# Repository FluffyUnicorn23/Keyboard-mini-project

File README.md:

PCB made with KiCAD, currently working on keyboard case and firmware

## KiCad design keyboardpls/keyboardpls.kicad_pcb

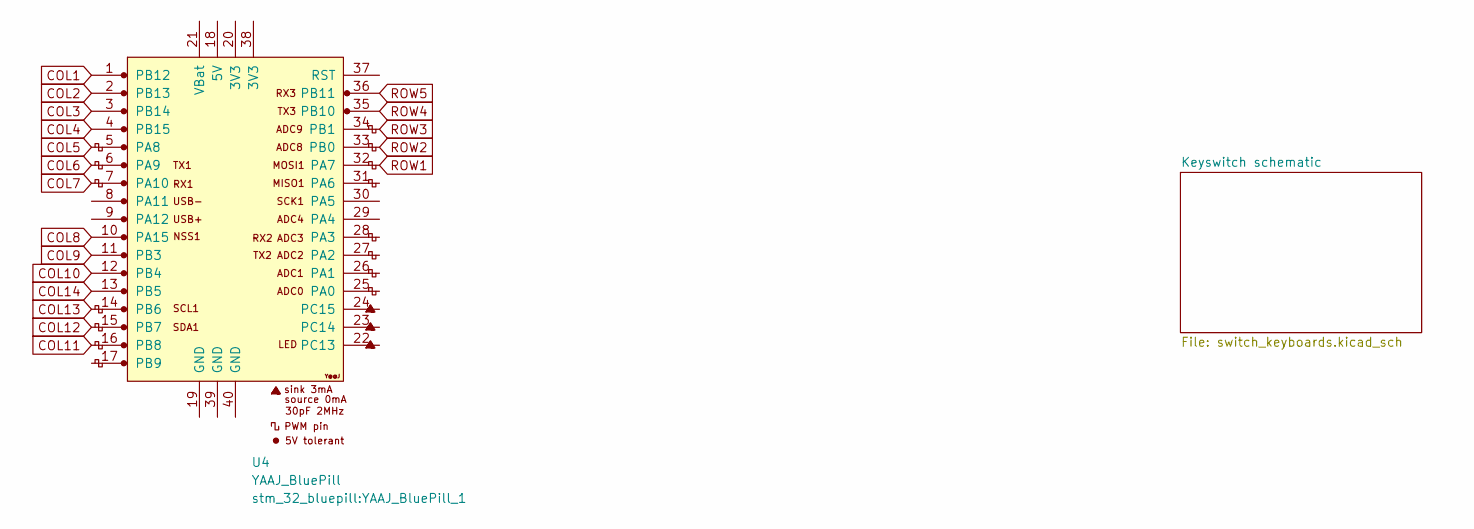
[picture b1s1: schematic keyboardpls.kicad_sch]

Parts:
U4: YAAJ_BluePill; YAAJ_BluePill_1

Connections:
COL1: U4.1 (PB12); also elsewhere on the board
COL2: U4.2 (PB13); also elsewhere on the board
COL3: U4.3 (PB14); also elsewhere on the board
COL4: U4.4 (PB15); also elsewhere on the board
COL5: U4.5 (PA8); also elsewhere on the board
COL6: U4.6 (PA9); also elsewhere on the board
COL7: U4.7 (PA10); also elsewhere on the board
COL8: U4.10 (PA15); also elsewhere on the board
COL9: U4.11 (PB3); also elsewhere on the board
COL10: U4.12 (PB4); also elsewhere on the board
COL11: U4.16 (PB8); also elsewhere on the board
COL12: U4.15 (PB7); also elsewhere on the board
COL13: U4.14 (PB6); also elsewhere on the board
COL14: U4.13 (PB5); also elsewhere on the board
ROW1: U4.32 (PA7); also elsewhere on the board
ROW2: U4.33 (PB0); also elsewhere on the board
ROW3: U4.34 (PB1); also elsewhere on the board
ROW4: U4.35 (PB10); also elsewhere on the board
ROW5: U4.36 (PB11); also elsewhere on the board

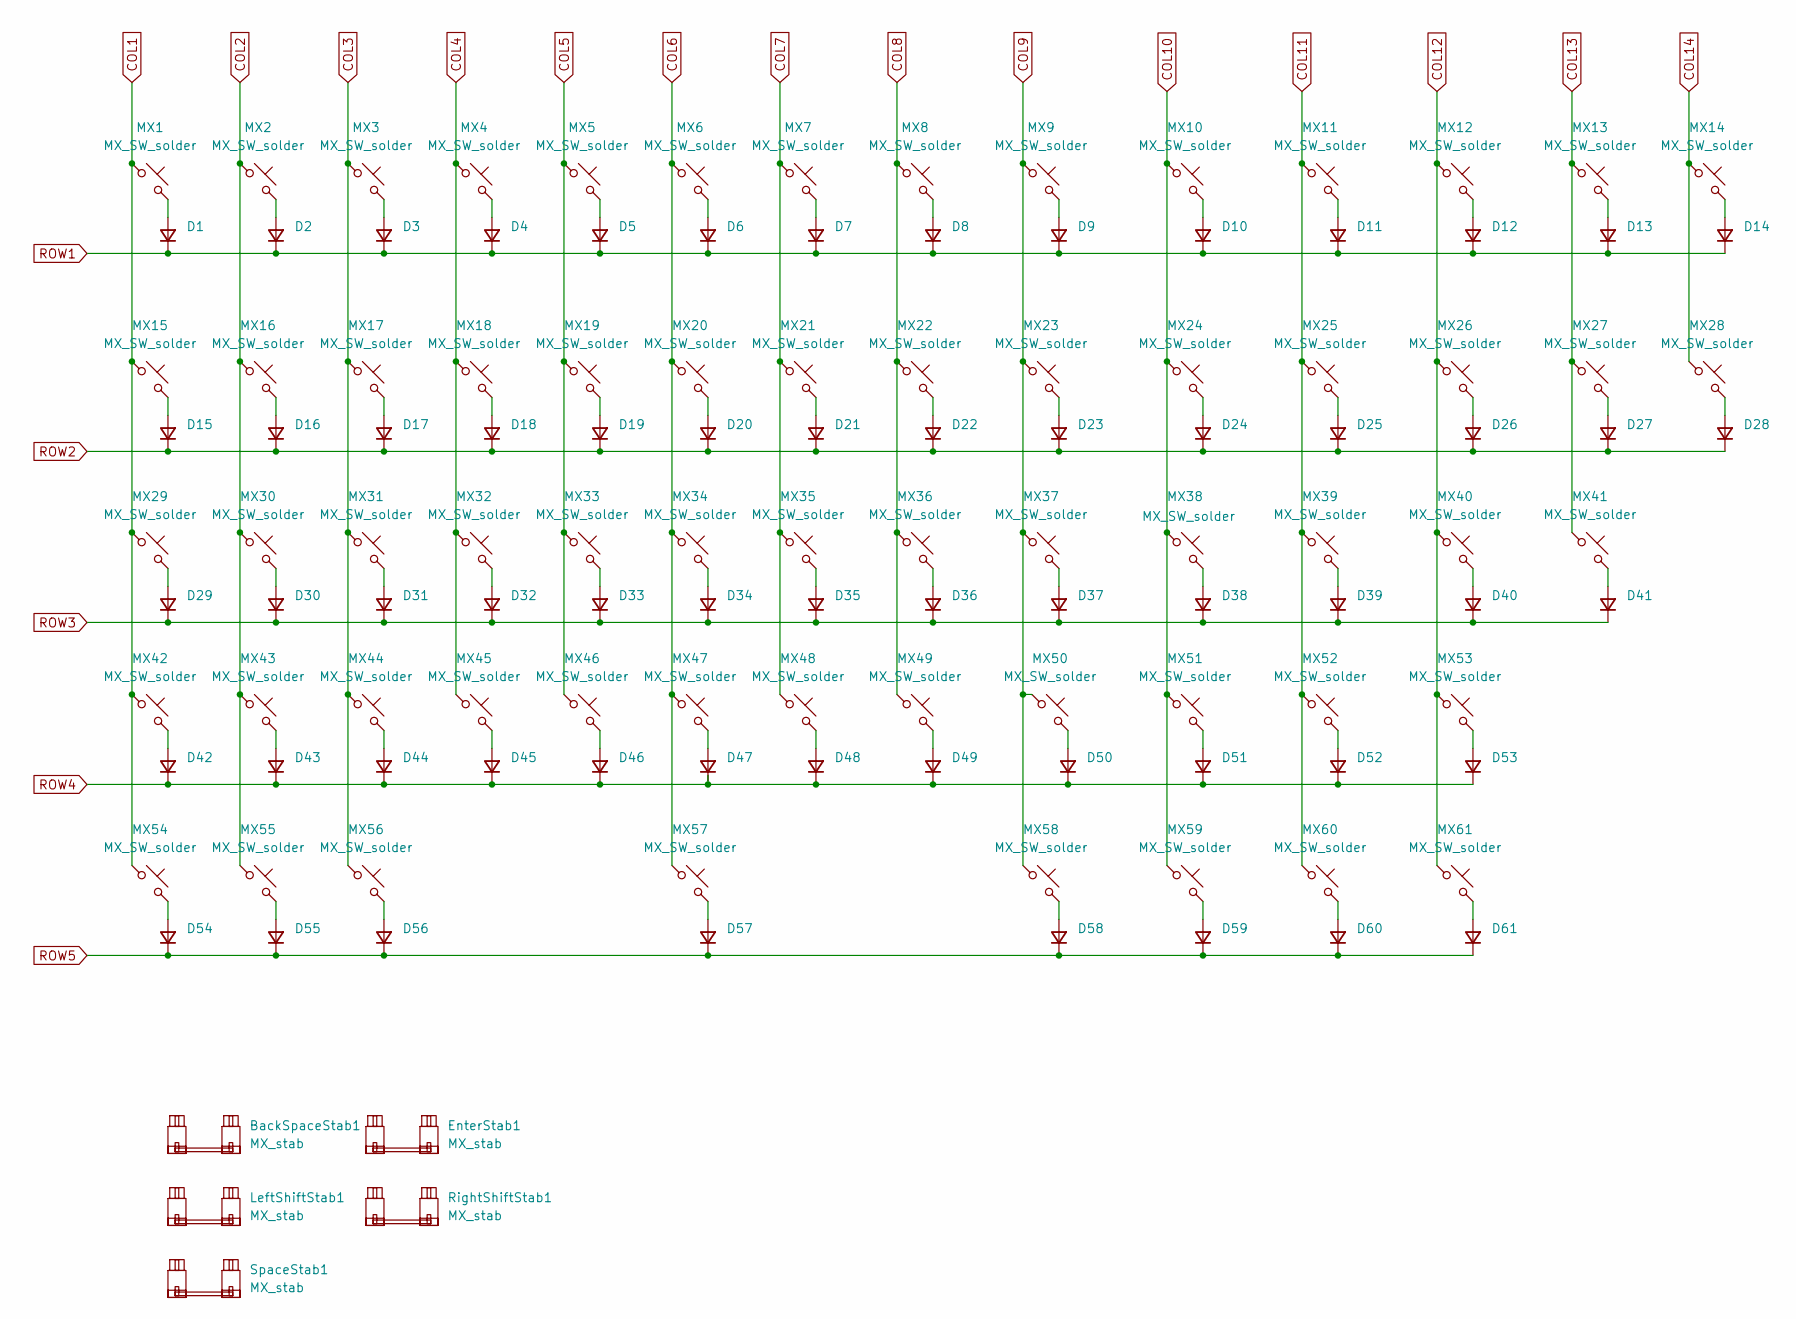
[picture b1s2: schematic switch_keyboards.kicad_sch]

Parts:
BackSpaceStab1: MX_stab; STAB_MX_P_2.25u
D1, D2, D3, D4, D5, D6, D7, D8, D9, D10, D11, D12, D13, D14, D15, D16, D17, D18, D19, D20, D21, D22, D23, D24, D25, D26, D27, D28, D29, D30, D31, D32, D33, D34, D35, D36, D37, D38, D39, D40, D41, D42, D43, D44, D45, D46, D47, D48, D49, D50, D51, D52, D53, D54, D55, D56, D57, D58, D59, D60, D61: D_Small; D_SOD-123
EnterStab1: MX_stab; STAB_MX_P_2.25u
LeftShiftStab1: MX_stab; STAB_MX_P_2.75u
MX1, MX2, MX3, MX4, MX5, MX6, MX7, MX8, MX9, MX10, MX11, MX12, MX13, MX14, MX15, MX16, MX17, MX18, MX19, MX20, MX21, MX22, MX23, MX24, MX25, MX26, MX27, MX28, MX29, MX30, MX31, MX32, MX33, MX34, MX35, MX36, MX37, MX38, MX39, MX40, MX41, MX42, MX43, MX44, MX45, MX46, MX47, MX48, MX49, MX50, MX51, MX52, MX53, MX54, MX55, MX56, MX57, MX58, MX59, MX60, MX61: MX_SW_solder; SW_MX_1u
RightShiftStab1: MX_stab; STAB_MX_P_2.75u
SpaceStab1: MX_stab; STAB_MX_P_6.25u

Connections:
COL1: MX1.1, MX15.1, MX29.1, MX42.1, MX54.1; also elsewhere on the board
COL2: MX2.1, MX16.1, MX30.1, MX43.1, MX55.1; also elsewhere on the board
COL3: MX3.1, MX17.1, MX31.1, MX44.1, MX56.1; also elsewhere on the board
COL4: MX4.1, MX18.1, MX32.1, MX45.1; also elsewhere on the board
COL5: MX5.1, MX19.1, MX33.1, MX46.1; also elsewhere on the board
COL6: MX6.1, MX20.1, MX34.1, MX47.1, MX57.1; also elsewhere on the board
COL7: MX7.1, MX21.1, MX35.1, MX48.1; also elsewhere on the board
COL8: MX8.1, MX22.1, MX36.1, MX49.1; also elsewhere on the board
COL9: MX9.1, MX23.1, MX37.1, MX50.1, MX58.1; also elsewhere on the board
COL10: MX10.1, MX24.1, MX38.1, MX51.1, MX59.1; also elsewhere on the board
COL11: MX11.1, MX25.1, MX39.1, MX52.1, MX60.1; also elsewhere on the board
COL12: MX12.1, MX26.1, MX40.1, MX53.1, MX61.1; also elsewhere on the board
COL13: MX13.1, MX27.1, MX41.1; also elsewhere on the board
COL14: MX14.1, MX28.1; also elsewhere on the board
unnamed: D1.2 (A), MX1.2
unnamed: D2.2 (A), MX2.2
unnamed: D3.2 (A), MX3.2
unnamed: D4.2 (A), MX4.2
unnamed: D5.2 (A), MX5.2
unnamed: D6.2 (A), MX6.2
unnamed: D7.2 (A), MX7.2
unnamed: D8.2 (A), MX8.2
unnamed: D9.2 (A), MX9.2
unnamed: D10.2 (A), MX10.2
unnamed: D11.2 (A), MX11.2
unnamed: D12.2 (A), MX12.2
unnamed: D13.2 (A), MX13.2
unnamed: D14.2 (A), MX14.2
unnamed: D15.2 (A), MX15.2
unnamed: D16.2 (A), MX16.2
unnamed: D17.2 (A), MX17.2
unnamed: D18.2 (A), MX18.2
unnamed: D19.2 (A), MX19.2
unnamed: D20.2 (A), MX20.2
unnamed: D21.2 (A), MX21.2
unnamed: D22.2 (A), MX22.2
unnamed: D23.2 (A), MX23.2
unnamed: D24.2 (A), MX24.2
unnamed: D25.2 (A), MX25.2
unnamed: D26.2 (A), MX26.2
unnamed: D27.2 (A), MX27.2
unnamed: D28.2 (A), MX28.2
unnamed: D29.2 (A), MX29.2
unnamed: D30.2 (A), MX30.2
unnamed: D31.2 (A), MX31.2
unnamed: D32.2 (A), MX32.2
unnamed: D33.2 (A), MX33.2
unnamed: D34.2 (A), MX34.2
unnamed: D35.2 (A), MX35.2
unnamed: D36.2 (A), MX36.2
unnamed: D37.2 (A), MX37.2
unnamed: D38.2 (A), MX38.2
unnamed: D39.2 (A), MX39.2
unnamed: D40.2 (A), MX40.2
unnamed: D41.2 (A), MX41.2
unnamed: D42.2 (A), MX42.2
unnamed: D43.2 (A), MX43.2
unnamed: D44.2 (A), MX44.2
unnamed: D45.2 (A), MX45.2
unnamed: D46.2 (A), MX46.2
unnamed: D47.2 (A), MX47.2
unnamed: D48.2 (A), MX48.2
unnamed: D49.2 (A), MX49.2
unnamed: D50.2 (A), MX50.2
unnamed: D51.2 (A), MX51.2
unnamed: D52.2 (A), MX52.2
unnamed: D53.2 (A), MX53.2
unnamed: D54.2 (A), MX54.2
unnamed: D55.2 (A), MX55.2
unnamed: D56.2 (A), MX56.2
unnamed: D57.2 (A), MX57.2
unnamed: D58.2 (A), MX58.2
unnamed: D59.2 (A), MX59.2
unnamed: D60.2 (A), MX60.2
unnamed: D61.2 (A), MX61.2
ROW1: D1.1 (K), D2.1 (K), D3.1 (K), D4.1 (K), D5.1 (K), D6.1 (K), D7.1 (K), D8.1 (K), D9.1 (K), D10.1 (K), D11.1 (K), D12.1 (K), D13.1 (K), D14.1 (K); also elsewhere on the board
ROW2: D15.1 (K), D16.1 (K), D17.1 (K), D18.1 (K), D19.1 (K), D20.1 (K), D21.1 (K), D22.1 (K), D23.1 (K), D24.1 (K), D25.1 (K), D26.1 (K), D27.1 (K), D28.1 (K); also elsewhere on the board
ROW3: D29.1 (K), D30.1 (K), D31.1 (K), D32.1 (K), D33.1 (K), D34.1 (K), D35.1 (K), D36.1 (K), D37.1 (K), D38.1 (K), D39.1 (K), D40.1 (K), D41.1 (K); also elsewhere on the board
ROW4: D42.1 (K), D43.1 (K), D44.1 (K), D45.1 (K), D46.1 (K), D47.1 (K), D48.1 (K), D49.1 (K), D50.1 (K), D51.1 (K), D52.1 (K), D53.1 (K); also elsewhere on the board
ROW5: D54.1 (K), D55.1 (K), D56.1 (K), D57.1 (K), D58.1 (K), D59.1 (K), D60.1 (K), D61.1 (K); also elsewhere on the board

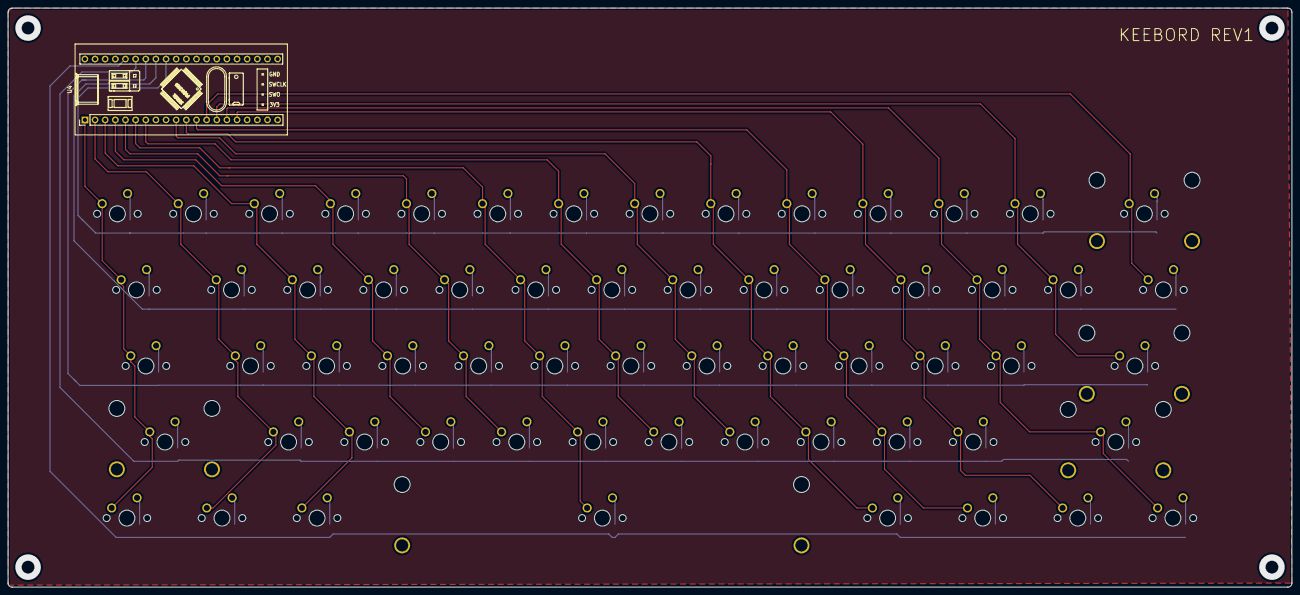
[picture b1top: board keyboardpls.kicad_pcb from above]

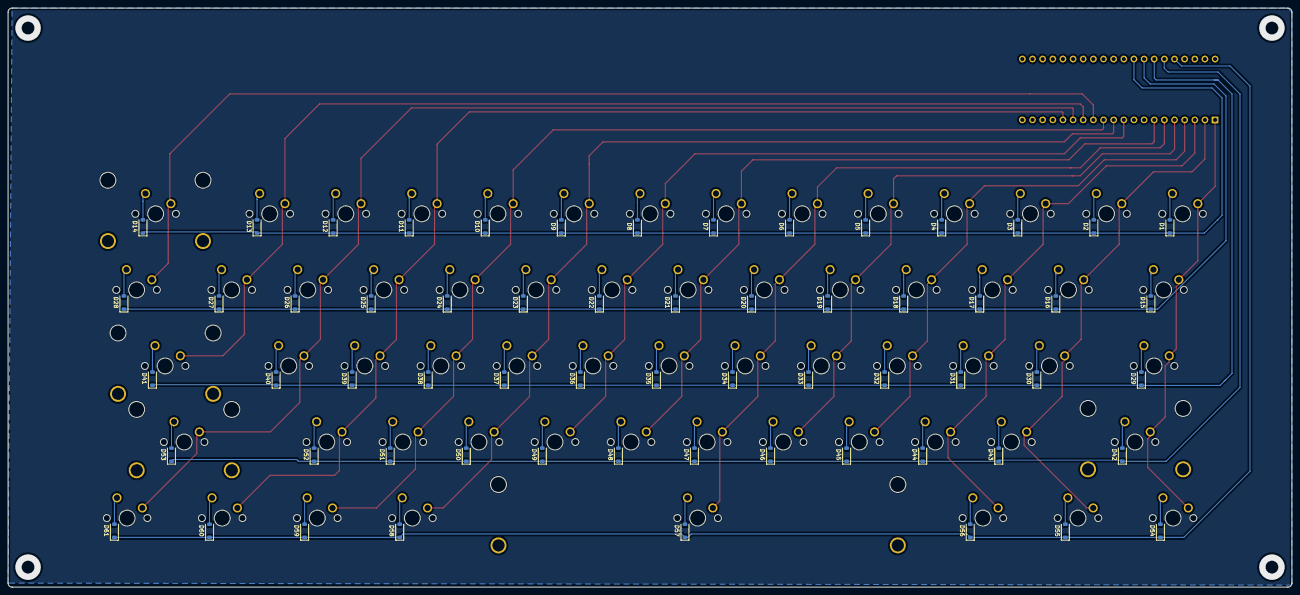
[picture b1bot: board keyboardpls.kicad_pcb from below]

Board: 2 copper layers, 321.5 x 145.0 mm, 128 parts (61 on the bottom side), 80 nets.

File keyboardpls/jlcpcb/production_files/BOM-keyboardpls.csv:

Comment,Designator,Footprint,LCSC,Quantity
MX_SW_solder,MX41,SW_MX_1u,,1
MX_SW_solder,MX23,SW_MX_1u,,1
MX_SW_solder,MX36,SW_MX_1u,,1
MX_SW_solder,MX3,SW_MX_1u,,1
MX_SW_solder,MX37,SW_MX_1u,,1
MX_SW_solder,MX14,SW_MX_1u,,1
MX_SW_solder,MX53,SW_MX_1u,,1
MX_SW_solder,MX56,SW_MX_1u,,1
MX_SW_solder,MX40,SW_MX_1u,,1
MX_SW_solder,MX33,SW_MX_1u,,1
MX_SW_solder,MX47,SW_MX_1u,,1
MX_SW_solder,MX16,SW_MX_1u,,1
MX_SW_solder,MX59,SW_MX_1u,,1
MX_stab,RightShiftStab1,STAB_MX_P_2.75u,,1
MX_SW_solder,MX18,SW_MX_1u,,1
MX_stab,BackSpaceStab1,STAB_MX_P_2.25u,,1
MX_stab,LeftShiftStab1,STAB_MX_P_2.75u,,1
MX_SW_solder,MX11,SW_MX_1u,,1
MX_SW_solder,MX12,SW_MX_1u,,1
MX_SW_solder,MX31,SW_MX_1u,,1
MX_SW_solder,MX30,SW_MX_1u,,1
MX_SW_solder,MX49,SW_MX_1u,,1
MX_SW_solder,MX57,SW_MX_1u,,1
MX_SW_solder,MX52,SW_MX_1u,,1
MX_stab,SpaceStab1,STAB_MX_P_6.25u,,1
MX_SW_solder,MX10,SW_MX_1u,,1
MX_SW_solder,MX54,SW_MX_1u,,1
MX_SW_solder,MX35,SW_MX_1u,,1
MX_SW_solder,MX9,SW_MX_1u,,1
MX_SW_solder,MX32,SW_MX_1u,,1
MX_SW_solder,MX19,SW_MX_1u,,1
MX_SW_solder,MX43,SW_MX_1u,,1
MX_stab,EnterStab1,STAB_MX_P_2.25u,,1
MX_SW_solder,MX2,SW_MX_1u,,1
MX_SW_solder,MX42,SW_MX_1u,,1
YAAJ_BluePill,U4,YAAJ_BluePill_1,,1
MX_SW_solder,MX60,SW_MX_1u,,1
MX_SW_solder,MX21,SW_MX_1u,,1
MX_SW_solder,MX34,SW_MX_1u,,1
MX_SW_solder,MX27,SW_MX_1u,,1
MX_SW_solder,MX28,SW_MX_1u,,1
MX_SW_solder,MX58,SW_MX_1u,,1
MX_SW_solder,MX5,SW_MX_1u,,1
MX_SW_solder,MX38,SW_MX_1u,,1
MX_SW_solder,MX61,SW_MX_1u,,1
MX_SW_solder,MX24,SW_MX_1u,,1
MX_SW_solder,MX48,SW_MX_1u,,1
MX_SW_solder,MX44,SW_MX_1u,,1
MX_SW_solder,MX1,SW_MX_1u,,1
MX_SW_solder,MX20,SW_MX_1u,,1
MX_SW_solder,MX4,SW_MX_1u,,1
MX_SW_solder,MX8,SW_MX_1u,,1
MX_SW_solder,MX55,SW_MX_1u,,1
MX_SW_solder,MX7,SW_MX_1u,,1
MX_SW_solder,MX22,SW_MX_1u,,1
MX_SW_solder,MX13,SW_MX_1u,,1
MX_SW_solder,MX51,SW_MX_1u,,1
MX_SW_solder,MX50,SW_MX_1u,,1
MX_SW_solder,MX29,SW_MX_1u,,1
MX_SW_solder,MX39,SW_MX_1u,,1
MX_SW_solder,MX15,SW_MX_1u,,1
MX_SW_solder,MX45,SW_MX_1u,,1
MX_SW_solder,MX17,SW_MX_1u,,1
MX_SW_solder,MX6,SW_MX_1u,,1
MX_SW_solder,MX26,SW_MX_1u,,1
MX_SW_solder,MX46,SW_MX_1u,,1
MX_SW_solder,MX25,SW_MX_1u,,1
D_Small,D14,D_SOD-123,,1
D_Small,D53,D_SOD-123,,1
D_Small,D50,D_SOD-123,,1
D_Small,D48,D_SOD-123,,1
D_Small,D19,D_SOD-123,,1
D_Small,D16,D_SOD-123,,1
D_Small,D27,D_SOD-123,,1
D_Small,D24,D_SOD-123,,1
D_Small,D23,D_SOD-123,,1
D_Small,D17,D_SOD-123,,1
D_Small,D43,D_SOD-123,,1
D_Small,D10,D_SOD-123,,1
D_Small,D26,D_SOD-123,,1
D_Small,D49,D_SOD-123,,1
D_Small,D35,D_SOD-123,,1
D_Small,D58,D_SOD-123,,1
D_Small,D29,D_SOD-123,,1
D_Small,D22,D_SOD-123,,1
D_Small,D15,D_SOD-123,,1
D_Small,D52,D_SOD-123,,1
D_Small,D3,D_SOD-123,,1
D_Small,D28,D_SOD-123,,1
D_Small,D20,D_SOD-123,,1
D_Small,D41,D_SOD-123,,1
D_Small,D33,D_SOD-123,,1
D_Small,D8,D_SOD-123,,1
D_Small,D2,D_SOD-123,,1
D_Small,D45,D_SOD-123,,1
D_Small,D18,D_SOD-123,,1
D_Small,D31,D_SOD-123,,1
D_Small,D56,D_SOD-123,,1
D_Small,D44,D_SOD-123,,1
D_Small,D11,D_SOD-123,,1
D_Small,D61,D_SOD-123,,1
D_Small,D37,D_SOD-123,,1
D_Small,D39,D_SOD-123,,1
D_Small,D13,D_SOD-123,,1
D_Small,D38,D_SOD-123,,1
D_Small,D21,D_SOD-123,,1
D_Small,D46,D_SOD-123,,1
D_Small,D9,D_SOD-123,,1
D_Small,D30,D_SOD-123,,1
D_Small,D5,D_SOD-123,,1
D_Small,D54,D_SOD-123,,1
D_Small,D59,D_SOD-123,,1
D_Small,D1,D_SOD-123,,1
D_Small,D25,D_SOD-123,,1
D_Small,D57,D_SOD-123,,1
D_Small,D32,D_SOD-123,,1
D_Small,D47,D_SOD-123,,1
D_Small,D4,D_SOD-123,,1
D_Small,D42,D_SOD-123,,1
D_Small,D55,D_SOD-123,,1
D_Small,D51,D_SOD-123,,1
D_Small,D34,D_SOD-123,,1
D_Small,D7,D_SOD-123,,1
D_Small,D60,D_SOD-123,,1
D_Small,D6,D_SOD-123,,1
D_Small,D12,D_SOD-123,,1
D_Small,D36,D_SOD-123,,1
D_Small,D40,D_SOD-123,,1
